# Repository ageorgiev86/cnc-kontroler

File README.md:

# CNC контролер на Orange Pi One

Универсален CNC контролер, изцяло собствена разработка: до 6 оси, шпиндел, магазин за инструменти, отделни входове за 3D пробник и toolsetter и затворен контур с енкодери.

Готовите програми (LinuxCNC, grblHAL, Mach3, arisc и др.) се използват само като справка за това как са решени отделните задачи. Кодът, протоколите и интерфейсът се пишат от нулата.

## Съдържание

| Файл | Какво има |
|---|---|
| [`LICENSE`](LICENSE) | Собственически лиценз: всички права запазени |
| [`THIRD_PARTY_NOTICES.md`](THIRD_PARTY_NOTICES.md) | Чужди компоненти, техните лицензи и правилата кодът да остане затворен |
| [`CLAUDE.md`](CLAUDE.md) | Кратък контекст за нови сесии с Claude Code: правила, решения, стил на работа |
| [`docs/arhitektura.md`](docs/arhitektura.md) | Хардуер, разделение Linux / MCU, енкодери, таймери, SPI протокол, периферия |
| [`docs/platki.md`](docs/platki.md) | Подходящи модели Orange Pi и Raspberry Pi, препоръки и правила за преносимост |
| [`docs/ui-iziskvania.md`](docs/ui-iziskvania.md) | Всички изисквания към интерфейса, екран по екран |
| [`docs/makrosi-logika.md`](docs/makrosi-logika.md) | Макроси, фонова логика и скриптове: разширение след стабилната версия |
| [`docs/otvoreni-vaprosi.md`](docs/otvoreni-vaprosi.md) | Неуточнени въпроси и следващи стъпки |
| [`docs/interpretator-planer.md`](docs/interpretator-planer.md) | Интерпретатор и планер на G-code: устройство, диалекти Mach3/Haas, стъпки |
| [`core/`](core/) | Ядро на C: интерпретатор и планер (тестове с `ctest`); инструкция в [`core/README.md`](core/README.md) |
| [`firmware/stm32/`](firmware/stm32/) | Firmware за STM32H723ZG (CMake, VS Code); инструкция в [`firmware/stm32/README.md`](firmware/stm32/README.md) |
| [`ui/maket.html`](ui/maket.html) | Интерактивен макет на интерфейса (отваря се в браузър) |

## Инсталиране на чиста система

На чист Armbian (Orange Pi) или Raspberry Pi OS Lite, като обикновения потребител:

```sh
sudo apt-get update && sudo apt-get install -y git
git clone https://github.com/ageorgiev86/cnc-kontroler.git
cd cnc-kontroler
sudo bash tools/cnc-install.sh            # интерфейсът, ядрото, услугата, USB, мрежата, логото
sudo reboot
```

Скриптът (`tools/cnc-install.sh`) пуска по ред отделните скриптове от `tools/`, компилира и проверява ядрото с тестовете му. Дневникът е в `install.log`. С `--readonly` включва и системата само за четене (за работа на машината), с `--no-splash` е без началния екран.

## Как се отваря макетът

Свали `ui/maket.html` и го отвори в браузър (Chrome, Edge, Firefox). Не е нужен сървър. Машината в макета е симулирана.

Публикувано копие (частно, вижда се само от собственика): https://claude.ai/artifact/83qwLJ9rhE3jGNBGYs3KNy

## Състояние

- [x] Избор на архитектура (Orange Pi / Raspberry Pi + STM32H723 по SPI)
- [x] Документация: архитектура, платки, входове и изходи 32 + 32, аналогови, RTC, лиценз
- [x] Интерактивен макет на интерфейса:
  - портретно и хоризонтално, 6 резолюции
  - фреза/рутер, лазер, плазма, струг; 3, 4 и 5 оси
  - позиции с енкодерна грешка, HOME, Go to 0, ръчно задаване на реф. точка
  - 3D траектория с цвят по инструмент
  - програми от памет, USB и мрежа; G-code с подпрограми (M98/M99), G81–83, G95/G96
  - Run from here с подготвителен ход, Rewind, изминало и оставащо време
  - магазин (карусел, верига, линеен), револвер за струг
  - пробинг (вкл. външен и вътрешен ъгъл), toolsetter
  - шпиндел по Modbus или PWM, входове и изходи 32 + 32, аналогови входове и изходи, мрежа
  - RESET (включване и реферирване), смазване, енкодери по оси, пробник встрани с калибриране
  - нива на достъп с PIN (Настройчик, Производител) и дневник на промените
- [ ] Armbian с PREEMPT_RT ядро и device tree overlays
- [ ] SPI протокол (спецификация)
- [x] Firmware за STM32: проект (CMake, HAL, такт, MPU, мигащ светодиод)
- [ ] Firmware за STM32: генериране на стъпки, енкодери, latch за пробник
- [ ] G-code интерпретатор и планер
- [ ] Истински интерфейс на LVGL
- [ ] Стабилна версия, тествана на машина
- [ ] Макроси и логика (обновяване)

Подробен план и отворени въпроси: [`docs/otvoreni-vaprosi.md`](docs/otvoreni-vaprosi.md).

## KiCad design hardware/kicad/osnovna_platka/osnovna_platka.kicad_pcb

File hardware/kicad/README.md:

# Платките (KiCad 10)

Схемите и разположението се **генерират със скриптове** (Python-а на KiCad), а не се чертаят на ръка. Така всяка промяна е повторяема и се проверява автоматично (ERC, DRC, застъпвания).

| Папка / файл | Какво е |
|---|---|
| `osnovna_platka/` | основната платка: STM32H723ZGT6, драйвери, енкодери, входове и изходи 8 + 8, шпиндел, Orange Pi (338 × 136 мм) |
| `razshiritel/` | разширителен модул: 8 входа + 8 изхода 24 V, верижно (93 × 64 мм) |
| `osnovna_platka.py` | схемата на основната платка (речникът `MCU` = изводите на STM32, съвпада с `firmware/stm32/Core/Inc/board.h`) |
| `platka.py` | разположението на основната платка по план (роли на елементите от схемата) |
| `razshiritel.py` | схемата и разположението на модула |
| `pravila.py` | правилата: класове мрежи (сигнал 0,4 мм, STM32 0,3 мм, захранване 1 мм, маси), преходи 0,6/1,2 мм |
| `trasirane.py` | пробно трасиране с Freerouting върху копие на проекта + заливки GND и GND_IO на двата слоя |
| `sch.py` | общата част на генератора на схеми |

## Пускане

Затвори KiCad без запис преди това (скриптовете презаписват файловете).

```
"C:\Program Files\KiCad\10.0\bin\python.exe" -I osnovna_platka.py osnovna_platka
"C:\Program Files\KiCad\10.0\bin\python.exe" -I pravila.py osnovna_platka
"C:\Program Files\KiCad\10.0\bin\python.exe" -I platka.py osnovna_platka 136
"C:\Program Files\KiCad\10.0\bin\python.exe" -I razshiritel.py razshiritel 64
```

Ако вече си трасирал или местил нещо ръчно в KiCad, **не пускай `platka.py`** (ще го изтрие). Промените по схемата тогава се пренасят с F8 (Update PCB from Schematic): връзката схема ↔ платка е по постоянни UUID.

## На Linux (и трасиране)

KiCad 10 от PPA-то на KiCad (Ubuntu 24.04), Java 21 и Freerouting 2.1.0 (2.5 иска Java 25):

```
sudo add-apt-repository ppa:kicad/kicad-10.0-releases
sudo apt install --no-install-recommends kicad kicad-footprints kicad-symbols openjdk-21-jre-headless
sudo mkdir -p /opt/freerouting
sudo curl -L -o /opt/freerouting/freerouting-2.1.0.jar \
    https://github.com/freerouting/freerouting/releases/download/v2.1.0/freerouting-2.1.0.jar
```

Скриптовете се пускат с Python-а, с който е компилиран модулът `pcbnew` (на Ubuntu 24.04 — `python3.12`):

```
python3.12 -I osnovna_platka.py osnovna_platka
python3.12 -I pravila.py osnovna_platka
python3.12 -I platka.py osnovna_platka 136
python3.12 -I trasirane.py osnovna_platka /tmp/trasirane --minutes 90
kicad-cli pcb drc --severity-all /tmp/trasirane/osnovna_platka.kicad_pcb
```

`trasirane.py` търси Freerouting и Java така: аргументите `--jar`/`--java`, после променливите
`FREEROUTING_JAR`/`FREEROUTING_JAVA`, после (Linux) най-новия `/opt/freerouting/freerouting-*.jar` и `java` от PATH,
(Windows) плъгина на KiCad. Пътищата до KiCad (символи, отпечатъци, `kicad-cli`) се сменят с `KICAD_DIR`,
`KICAD_SYMBOL_DIR`, `KICAD_FOOTPRINT_DIR`, `KICAD_CLI`. Ако ERC/DRC се оплакват „library not included“, копирай
`/usr/share/kicad/template/{sym,fp}-lib-table` в `~/.config/kicad/10.0/`.

Freerouting 2.1 не спира по броя проходи (`-mp` се пренебрегва), а само по време: `--minutes N` (или
`FREEROUTING_MINUTES`, по подразбиране 60). Напредъкът е в `<копие>/freerouting.log` („pass #… (N unrouted)“).
Преди Freerouting `trasirane.py` слага преходите към масата (при QFP навътре под корпуса) и заключени изводи навън
по 1,5 мм от всеки сигнален извод на STM32 (fan-out: иначе рано сложено трасе покрай изводите запушва изхода на
останалите); след него маха висящите парчета и пълни масите (клемите — плътно към заливката).

След Freerouting остатъкът се довършва с `doveshvane.py` (собствен рутер: мрежа 0,05 мм, A* на двата слоя,
разкъсване на чужди трасета до 3 мм от краищата; `doveshvane.c` се компилира при пускане с `cc`/`gcc`):

```
python3.12 -I doveshvane.py /tmp/trasirane/osnovna_platka.kicad_pcb /tmp/trasirane/dovarshena.kicad_pcb
```

Пази платката с най-малко несвързани и без грешки в DRC. Резултатът е в `osnovna_platka/trasirana/`.

`pravila.py` записва и `osnovna_platka.kicad_dru`: 0,2 мм при всичко в U1 (изводите на STM32 са на 0,2 мм един от друг
и при масата и неизползваните изводи).

## Правила за домашно производство

- Двуслойна, фоторезист; метализирани отвори; най-малкото свредло 0,5 мм → преход с отвор 0,6 мм и площадка 1,2 мм.
- 0,2 мм разстояние само при изводите на STM32 (LQFP144, стъпка 0,5 мм), иначе 0,25 мм.
- Масите (GND за логиката, GND_IO за изолираната 24 V част) са заливка на двата слоя и служат и като екран; между тях 2 мм по изолационната граница (пунктир на копринения слой).

## План на основната платка

- **Горе:** всички изходи: 6 драйвера (клеми +5V, STEP, DIR, ENA, ALM, GND), честотен регулатор, RS485, изходи 1–8.
- **Долу:** всички входове: 7 енкодера (+5V, 0V, A, B), MPG пулт (гнездо 2 × 3), авариен стоп на пулта, пробник/toolsetter/авариен стоп, крайни изключватели и HOME (14 клеми).
- **Вляво:** 24 V, PE, USB-B и захранването (в посоката на тока). **Вдясно:** 24 V за датчиците, входове 1–8, гнездо за разширителните модули.
- Клемите са едноетажни щепселни 5,08 мм (Phoenix MSTBA), 1 мм една от друга.
- Изходите и входовете са свързани по физическия ред на изводите на чиповете (без кръстосване): буферите към драйверите са 74ACT541 (проходни изводи); при 74HCT165 таблицата „клема → бит“ е в `board.h`.

## Преди производство

Схемата е проектирана по документацията на чиповете, но преди поръчка/изработка трябва да я прегледа човек с опит в платки. Отворено: окончателното трасиране и модулът на MPG пулта (последен).

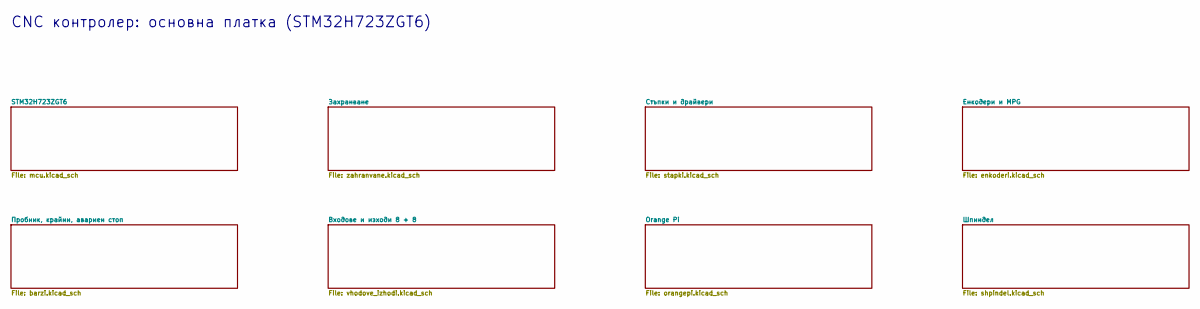
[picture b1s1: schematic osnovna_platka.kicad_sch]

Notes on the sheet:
CNC контролер: основна платка (STM32H723ZGT6)

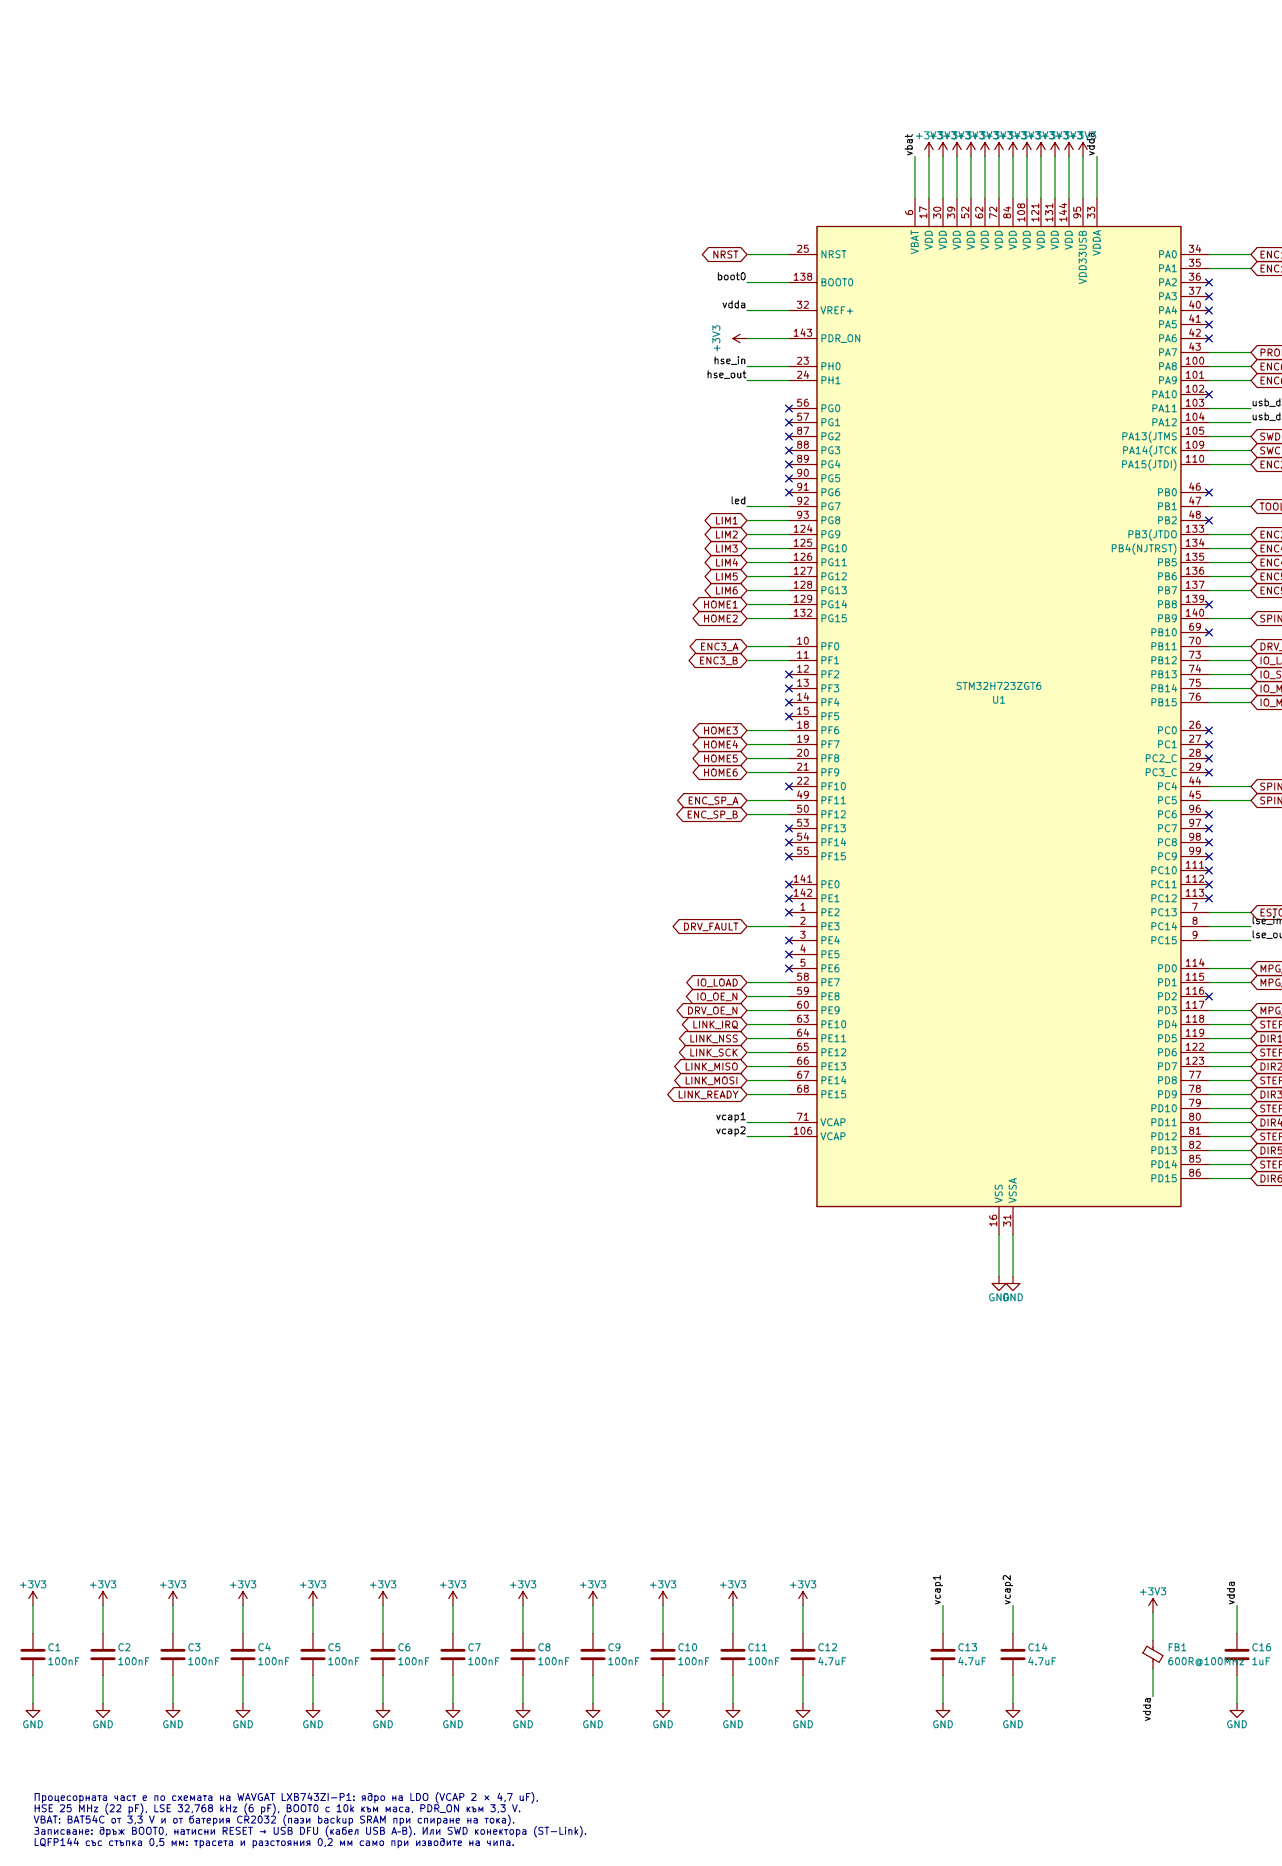
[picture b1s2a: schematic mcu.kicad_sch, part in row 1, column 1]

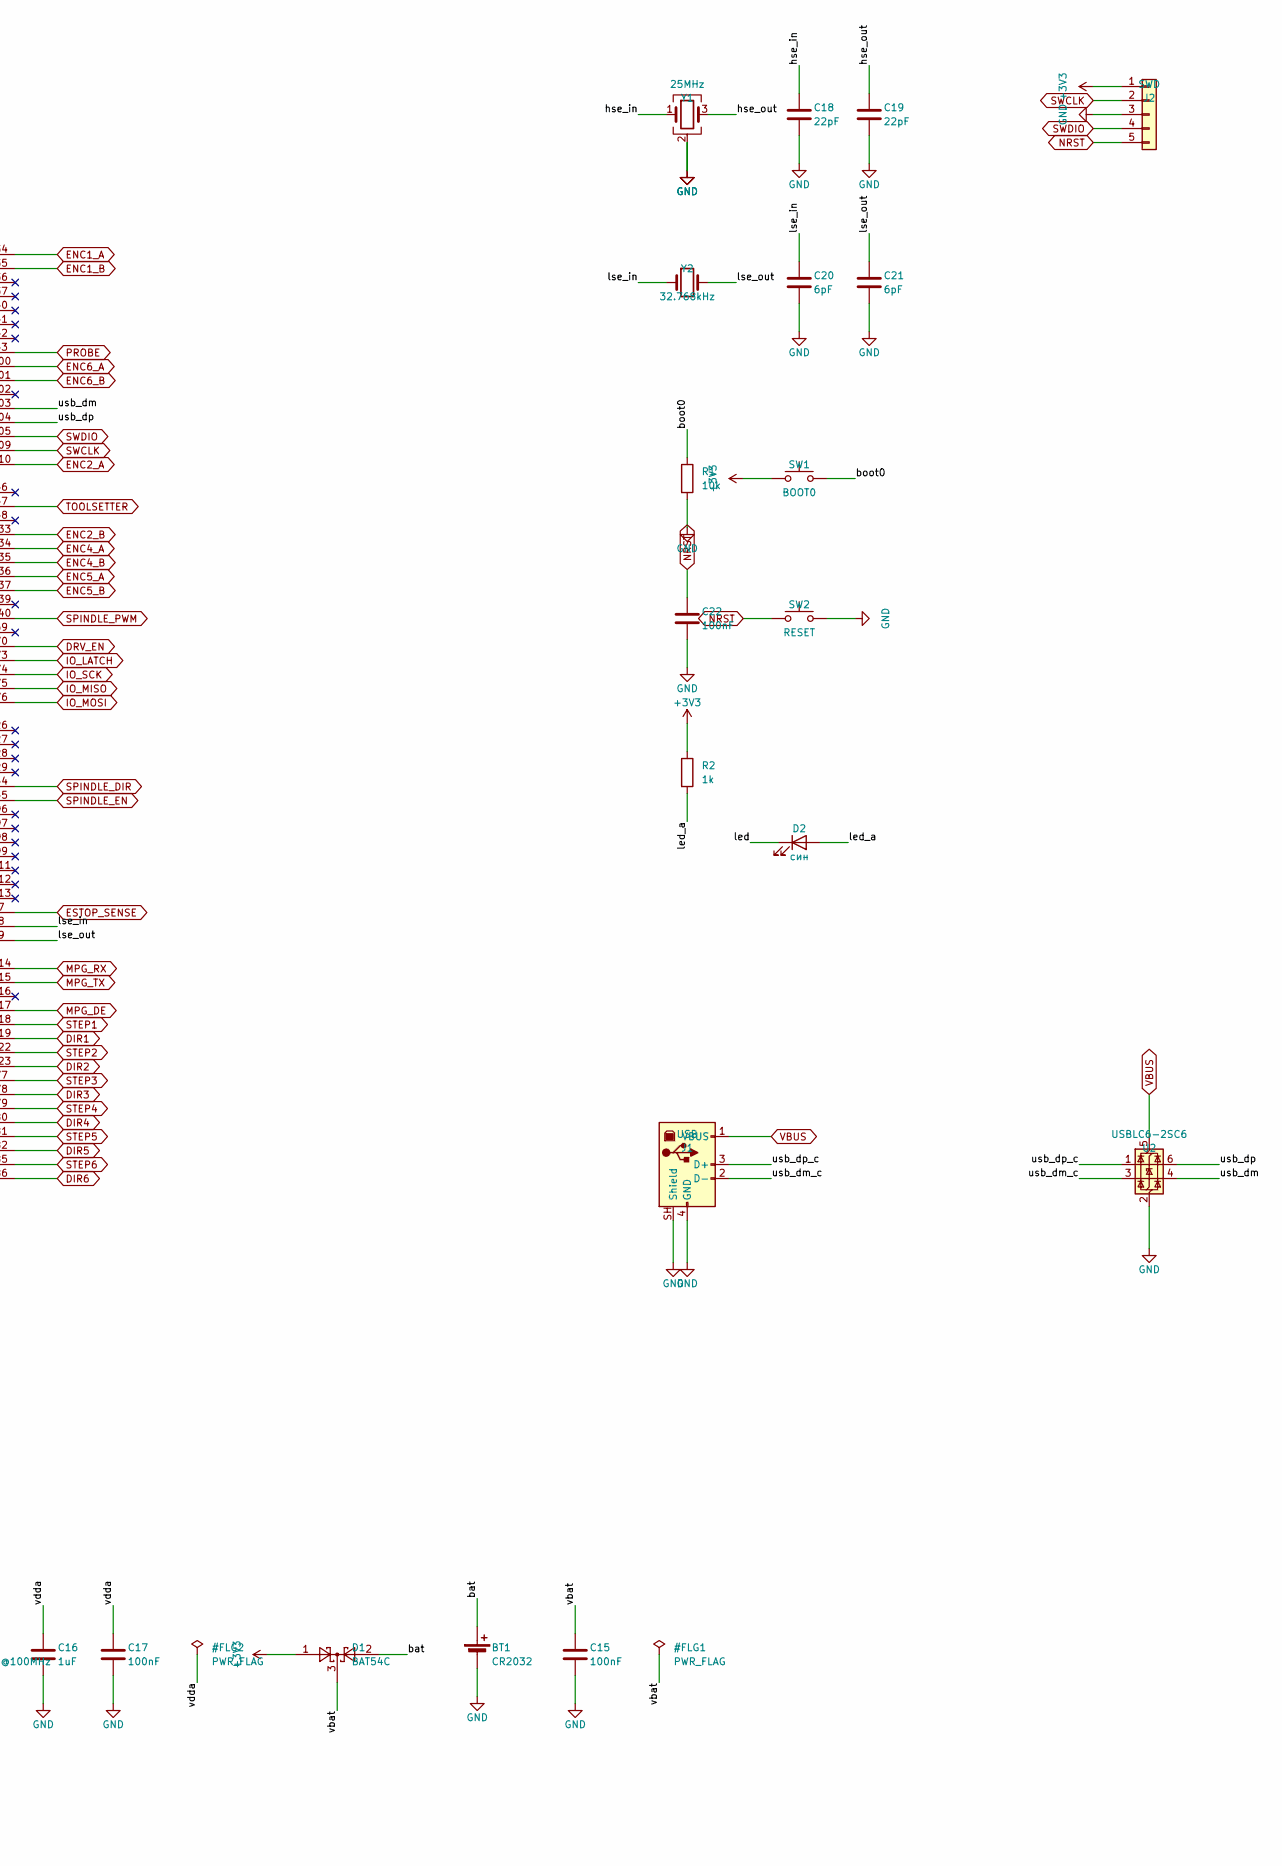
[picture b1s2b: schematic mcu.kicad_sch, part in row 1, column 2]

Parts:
BT1: CR2032; BatteryHolder_Keystone_3002_1x2032
C1, C2, C3, C4, C5, C6, C7, C8, C9, C10, C11, C15, C17, C22: 100nF; C_0805_2012Metric
C12, C13, C14: 4.7uF; C_1206_3216Metric
C16: 1uF; C_0805_2012Metric
C18, C19: 22pF; C_0805_2012Metric
C20, C21: 6pF; C_0805_2012Metric
D1: BAT54C; SOT-23
D2: син; LED_0805_2012Metric
FB1: 600R@100MHz; L_0805_2012Metric
J1: USB; USB_B_OST_USB-B1HSxx_Horizontal
J2: SWD; PinHeader_1x05_P2.54mm_Vertical
R1: 10k; R_0805_2012Metric
R2: 1k; R_0805_2012Metric
SW1: BOOT0; SW_SPST_TL3342
SW2: RESET; SW_SPST_TL3342
U1: STM32H723ZGT6; LQFP-144_20x20mm_P0.5mm
U2: USBLC6-2SC6; SOT-23-6
Y1: 25MHz; Crystal_SMD_3225-4Pin_3.2x2.5mm
Y2: 32.768kHz; Crystal_SMD_3215-2Pin_3.2x1.5mm

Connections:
+3V3: C1.1, C2.1, C3.1, C4.1, C5.1, C6.1, C7.1, C8.1, C9.1, C10.1, C11.1, C12.1, D1.1, FB1.1, J2.1, R2.1, SW1.1, U1.17 (VDD), U1.30 (VDD), U1.39 (VDD), U1.52 (VDD), U1.62 (VDD), U1.72 (VDD), U1.84 (VDD), U1.95 (VDD33USB), U1.108 (VDD), U1.121 (VDD), U1.131 (VDD), U1.143 (PDR_ON), U1.144 (VDD); also elsewhere on the board
/STM32H723ZGT6/bat: BT1.1 (+), D1.2
/STM32H723ZGT6/boot0: R1.1, SW1.2, U1.138 (BOOT0)
/STM32H723ZGT6/hse_in: C18.1, U1.23 (PH0), Y1.1
/STM32H723ZGT6/hse_out: C19.1, U1.24 (PH1), Y1.3
/STM32H723ZGT6/led: D2.1 (K), U1.92 (PG7)
/STM32H723ZGT6/led_a: D2.2 (A), R2.2
/STM32H723ZGT6/lse_in: C20.1, U1.8 (PC14), Y2.1
/STM32H723ZGT6/lse_out: C21.1, U1.9 (PC15), Y2.2
/STM32H723ZGT6/usb_dm: U1.103 (PA11), U2.4 (I/O2)
/STM32H723ZGT6/usb_dm_c: J1.2 (D-), U2.3 (I/O2)
/STM32H723ZGT6/usb_dp: U1.104 (PA12), U2.6 (I/O1)
/STM32H723ZGT6/usb_dp_c: J1.3 (D+), U2.1 (I/O1)
/STM32H723ZGT6/vbat: C15.1, D1.3, U1.6 (VBAT)
/STM32H723ZGT6/vcap1: C13.1, U1.71 (VCAP)
/STM32H723ZGT6/vcap2: C14.1, U1.106 (VCAP)
/STM32H723ZGT6/vdda: C16.1, C17.1, FB1.2, U1.32 (VREF+), U1.33 (VDDA)
DIR1: U1.119 (PD5); also elsewhere on the board
DIR2: U1.123 (PD7); also elsewhere on the board
DIR3: U1.78 (PD9); also elsewhere on the board
DIR4: U1.80 (PD11); also elsewhere on the board
DIR5: U1.82 (PD13); also elsewhere on the board
DIR6: U1.86 (PD15); also elsewhere on the board
DRV_EN: U1.70 (PB11); also elsewhere on the board
DRV_FAULT: U1.2 (PE3); also elsewhere on the board
DRV_OE_N: U1.60 (PE9); also elsewhere on the board
ENC1_A: U1.34 (PA0); also elsewhere on the board
ENC1_B: U1.35 (PA1); also elsewhere on the board
ENC2_A: U1.110 (PA15(JTDI)); also elsewhere on the board
ENC2_B: U1.133 (PB3(JTDO); also elsewhere on the board
ENC3_A: U1.10 (PF0); also elsewhere on the board
ENC3_B: U1.11 (PF1); also elsewhere on the board
ENC4_A: U1.134 (PB4(NJTRST)); also elsewhere on the board
ENC4_B: U1.135 (PB5); also elsewhere on the board
ENC5_A: U1.136 (PB6); also elsewhere on the board
ENC5_B: U1.137 (PB7); also elsewhere on the board
ENC6_A: U1.100 (PA8); also elsewhere on the board
ENC6_B: U1.101 (PA9); also elsewhere on the board
ENC_SP_A: U1.49 (PF11); also elsewhere on the board
ENC_SP_B: U1.50 (PF12); also elsewhere on the board
ESTOP_SENSE: U1.7 (PC13); also elsewhere on the board
GND: BT1.2 (-), C1.2, C2.2, C3.2, C4.2, C5.2, C6.2, C7.2, C8.2, C9.2, C10.2, C11.2, C12.2, C13.2, C14.2, C15.2, C16.2, C17.2, C18.2, C19.2, C20.2, C21.2, C22.2, J1.4 (GND), J1.SH (Shield), J2.3, R1.2, SW2.2, U1.16 (VSS), U1.31 (VSSA), U1.38 (VSS), U1.51 (VSS), U1.61 (VSS), U1.83 (VSS), U1.94 (VSS), U1.107 (VSS), U1.120 (VSS), U1.130 (VSS), U2.2 (GND), Y1.2 (G), Y1.4 (G); also elsewhere on the board
HOME1: U1.129 (PG14); also elsewhere on the board
HOME2: U1.132 (PG15); also elsewhere on the board
HOME3: U1.18 (PF6); also elsewhere on the board
HOME4: U1.19 (PF7); also elsewhere on the board
HOME5: U1.20 (PF8); also elsewhere on the board
HOME6: U1.21 (PF9); also elsewhere on the board
IO_LATCH: U1.73 (PB12); also elsewhere on the board
IO_LOAD: U1.58 (PE7); also elsewhere on the board
IO_MISO: U1.75 (PB14); also elsewhere on the board
IO_MOSI: U1.76 (PB15); also elsewhere on the board
IO_OE_N: U1.59 (PE8); also elsewhere on the board
IO_SCK: U1.74 (PB13); also elsewhere on the board
LIM1: U1.93 (PG8); also elsewhere on the board
LIM2: U1.124 (PG9); also elsewhere on the board
LIM3: U1.125 (PG10); also elsewhere on the board
LIM4: U1.126 (PG11); also elsewhere on the board
LIM5: U1.127 (PG12); also elsewhere on the board
LIM6: U1.128 (PG13); also elsewhere on the board
LINK_IRQ: U1.63 (PE10); also elsewhere on the board
LINK_MISO: U1.66 (PE13); also elsewhere on the board
LINK_MOSI: U1.67 (PE14); also elsewhere on the board
LINK_NSS: U1.64 (PE11); also elsewhere on the board
LINK_READY: U1.68 (PE15); also elsewhere on the board
LINK_SCK: U1.65 (PE12); also elsewhere on the board
MPG_DE: U1.117 (PD3); also elsewhere on the board
MPG_RX: U1.114 (PD0); also elsewhere on the board
MPG_TX: U1.115 (PD1); also elsewhere on the board
NRST: C22.1, J2.5, SW2.1, U1.25 (NRST)
PROBE: U1.43 (PA7); also elsewhere on the board
SPINDLE_DIR: U1.44 (PC4); also elsewhere on the board
SPINDLE_EN: U1.45 (PC5); also elsewhere on the board
SPINDLE_PWM: U1.140 (PB9); also elsewhere on the board
STEP1: U1.118 (PD4); also elsewhere on the board
STEP2: U1.122 (PD6); also elsewhere on the board
STEP3: U1.77 (PD8); also elsewhere on the board
STEP4: U1.79 (PD10); also elsewhere on the board
STEP5: U1.81 (PD12); also elsewhere on the board
STEP6: U1.85 (PD14); also elsewhere on the board
SWCLK: J2.2, U1.109 (PA14(JTCK)
SWDIO: J2.4, U1.105 (PA13(JTMS)
TOOLSETTER: U1.47 (PB1); also elsewhere on the board
VBUS: J1.1 (VBUS), U2.5 (VBUS); also elsewhere on the board

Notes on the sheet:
Процесорната част е по схемата на WAVGAT LXB743ZI-P1: ядро на LDO (VCAP 2 × 4,7 uF), HSE 25 MHz (22 pF), LSE 32,768 kHz (6 pF), BOOT0 с 10k към маса, PDR_ON към 3,3 V. VBAT: BAT54C от 3,3 V и от батерия CR2032 (пази backup SRAM при спиране на тока). Записване: дръж BOOT0, натисни RESET → USB DFU (к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

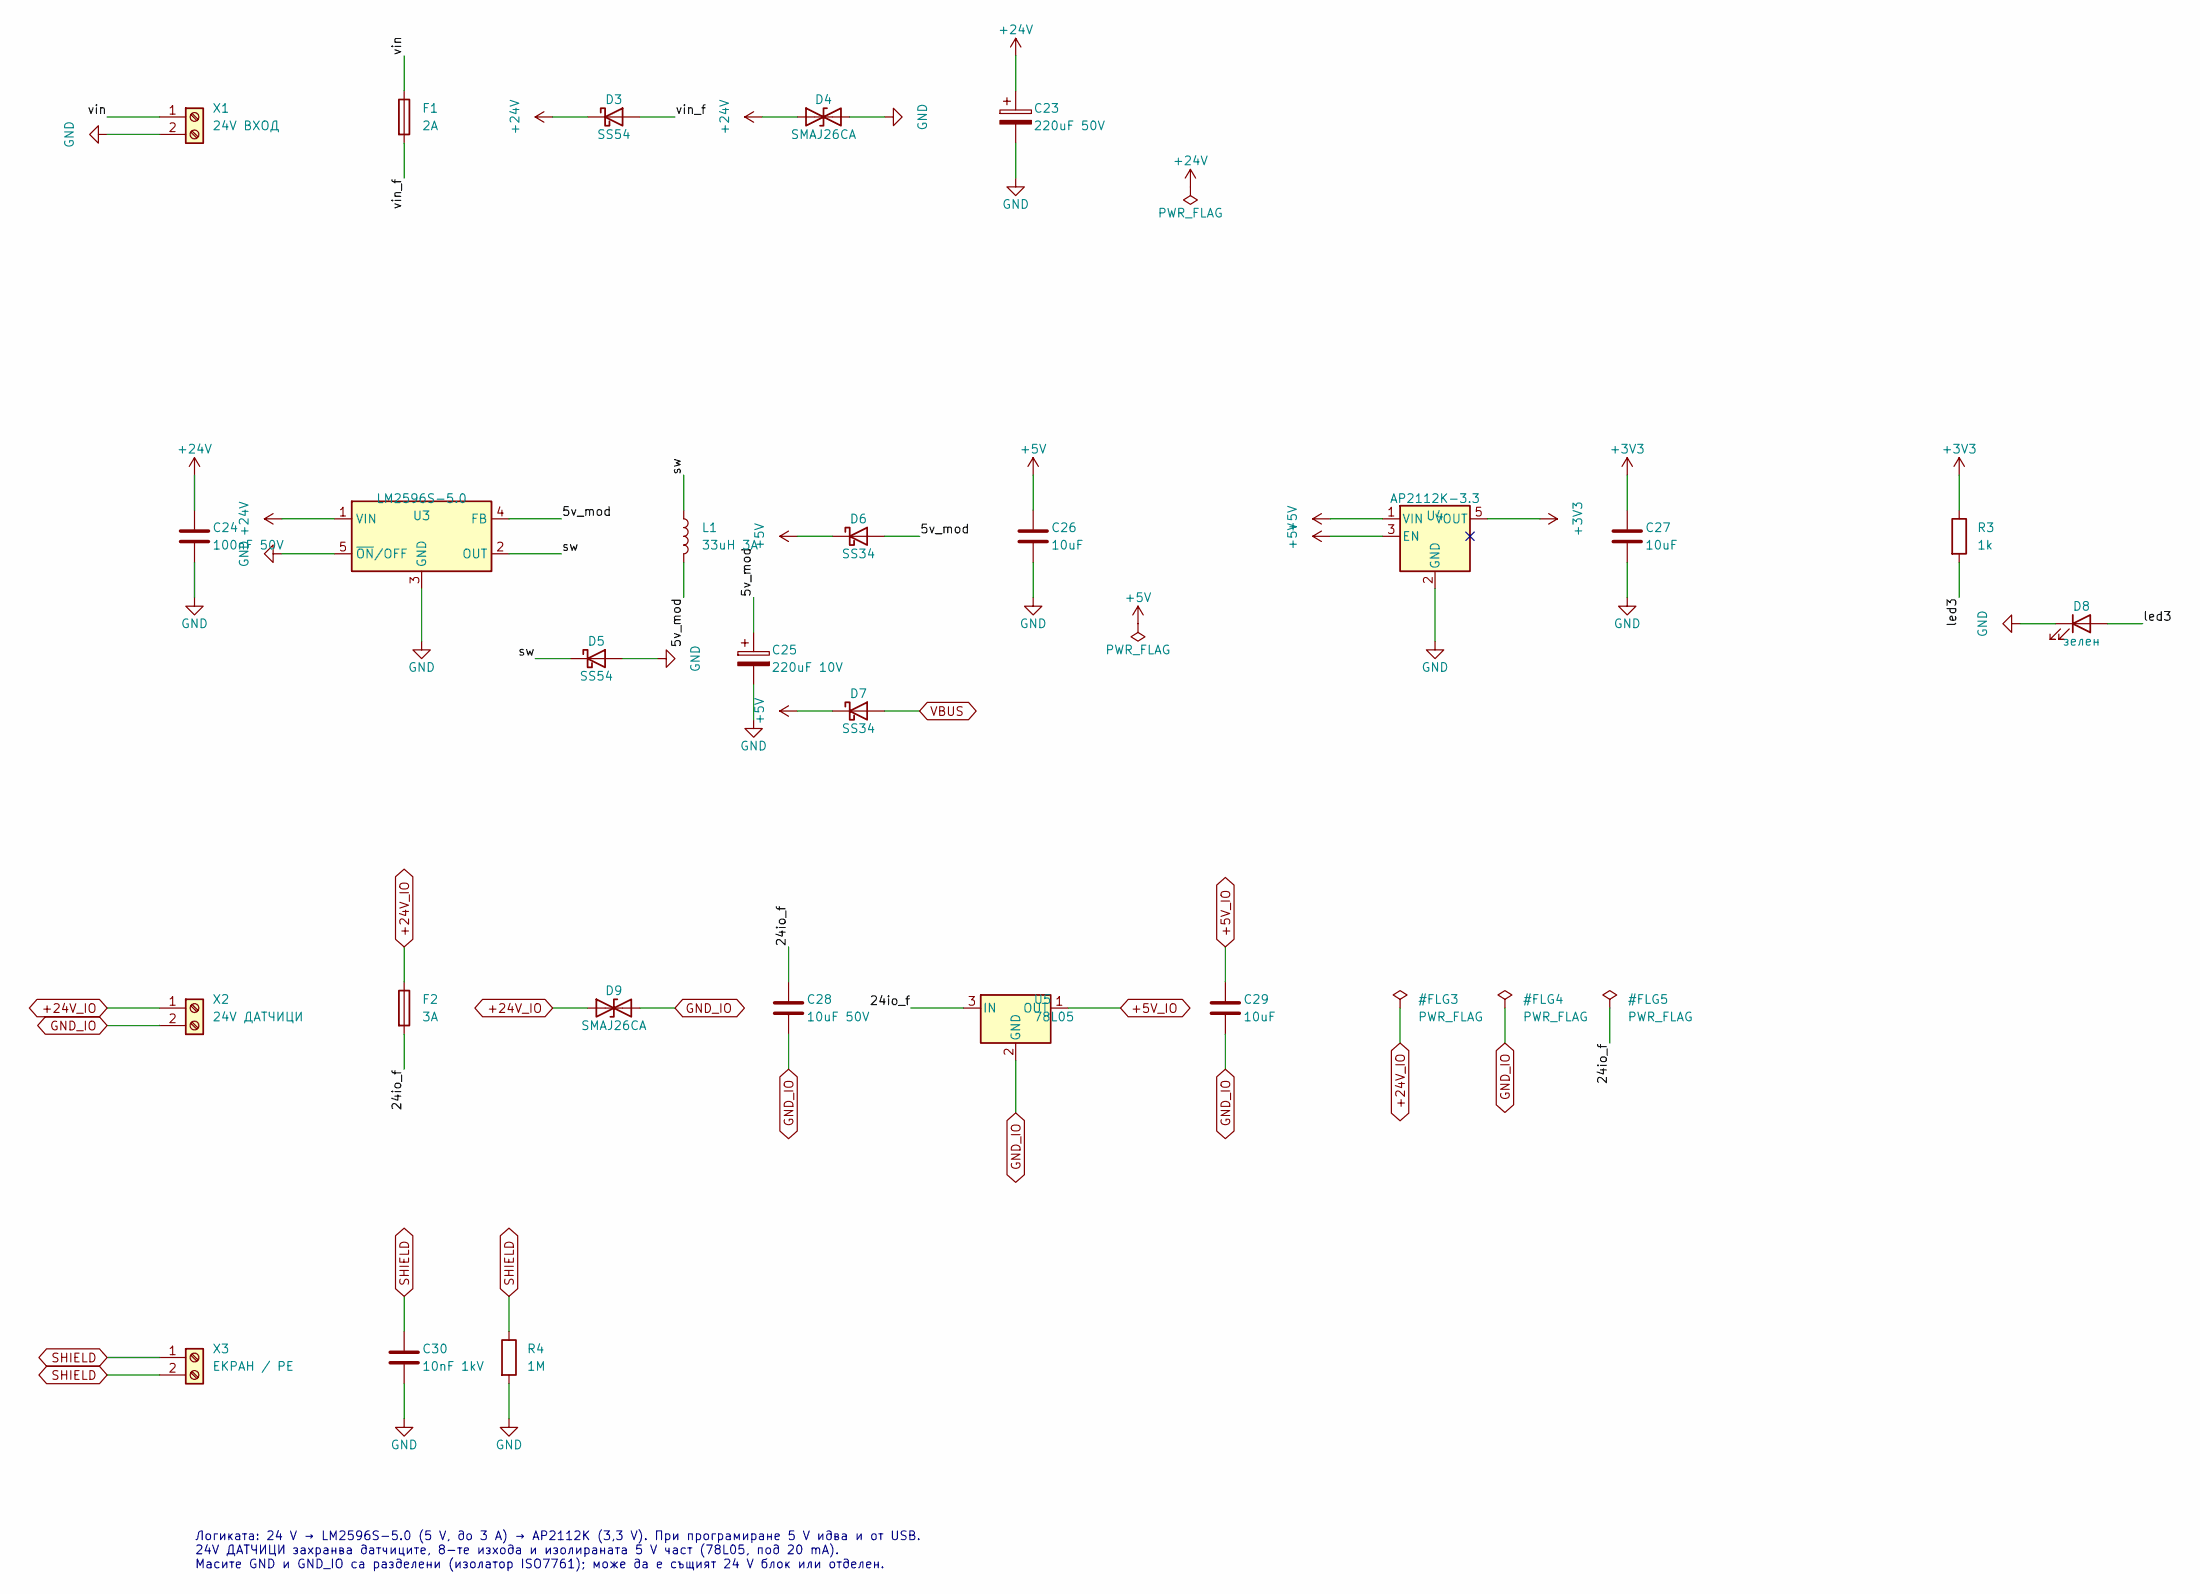
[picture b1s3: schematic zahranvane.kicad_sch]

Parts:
C23: 220uF 50V; CP_Elec_10x10.5
C24: 100nF 50V; C_0805_2012Metric
C25: 220uF 10V; CP_Elec_8x10
C26, C27, C29: 10uF; C_1206_3216Metric
C28: 10uF 50V; C_1210_3225Metric
C30: 10nF 1kV; C_1206_3216Metric
D3, D5: SS54; D_SMC
D4, D9: SMAJ26CA; D_SMA
D6, D7: SS34; D_SMA
D8: зелен; LED_0805_2012Metric
F1: 2A; Fuse_1812_4532Metric
F2: 3A; Fuse_1812_4532Metric
L1: 33uH 3A; L_12x12mm_H8mm
R3: 1k; R_0805_2012Metric
R4: 1M; R_1206_3216Metric
U3: LM2596S-5.0; TO-263-5_TabPin3
U4: AP2112K-3.3; SOT-23-5
U5: 78L05; SOT-89-3
X1: 24V ВХОД; PhoenixContact_MSTBA_2,5_2-G-5,08_1x02_P5.08mm_Horizontal
X2: 24V ДАТЧИЦИ; PhoenixContact_MSTBA_2,5_2-G-5,08_1x02_P5.08mm_Horizontal
X3: ЕКРАН / PE; PhoenixContact_MSTBA_2,5_2-G-5,08_1x02_P5.08mm_Horizontal

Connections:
+3V3: C27.1, R3.1, U4.5 (VOUT); also elsewhere on the board
+5V: C26.1, D6.1 (K), D7.1 (K), U4.1 (VIN), U4.3 (EN); also elsewhere on the board
+5V_IO: C29.1, U5.1 (OUT); also elsewhere on the board
+24V: C23.1, C24.1, D3.1 (K), D4.1 (A1), U3.1 (VIN); also elsewhere on the board
+24V_IO: D9.1 (A1), F2.1, X2.1; also elsewhere on the board
/Захранване/5v_mod: C25.1, D6.2 (A), L1.2, U3.4 (FB)
/Захранване/24io_f: C28.1, F2.2, U5.3 (IN)
/Захранване/led3: D8.2 (A), R3.2
/Захранване/sw: D5.1 (K), L1.1, U3.2 (OUT)
/Захранване/vin: F1.1, X1.1
/Захранване/vin_f: D3.2 (A), F1.2
GND: C23.2, C24.2, C25.2, C26.2, C27.2, C30.2, D4.2 (A2), D5.2 (A), D8.1 (K), R4.2, U3.3 (GND), U3.5 (~ON/OFF), U4.2 (GND), X1.2; also elsewhere on the board
GND_IO: C28.2, C29.2, D9.2 (A2), U5.2 (GND), X2.2; also elsewhere on the board
SHIELD: C30.1, R4.1, X3.1, X3.2
VBUS: D7.2 (A); also elsewhere on the board

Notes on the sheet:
Логиката: 24 V → LM2596S-5.0 (5 V, до 3 A) → AP2112K (3,3 V). При програмиране 5 V идва и от USB. 24V ДАТЧИЦИ захранва датчиците, 8-те изхода и изолираната 5 V част (78L05, под 20 mA). Масите GND и GND_IO са разделени (изолатор ISO7761); може да е същият 24 V блок или отделен.

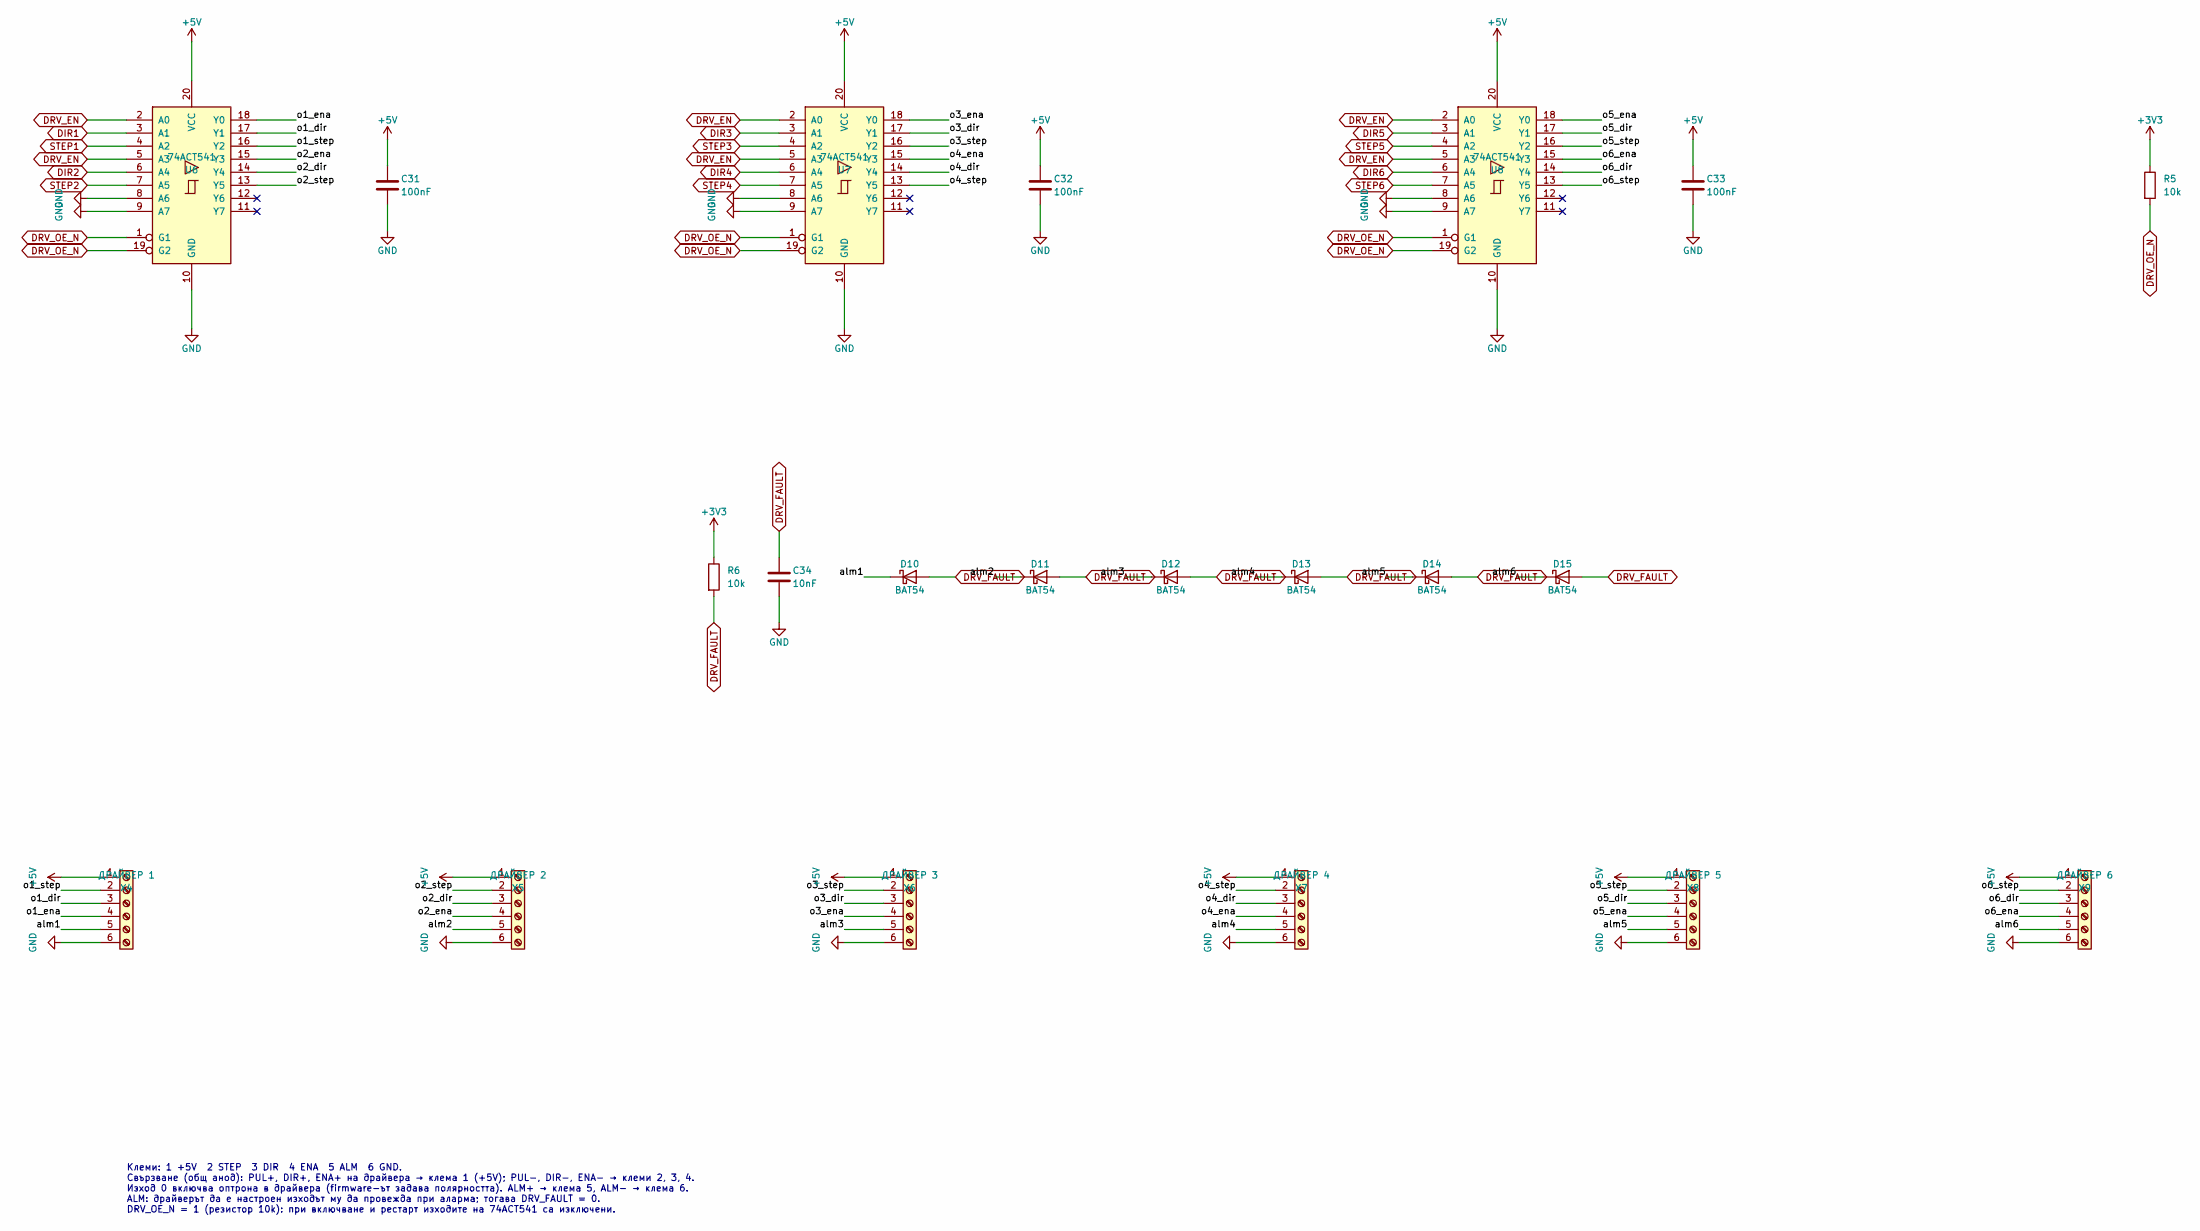
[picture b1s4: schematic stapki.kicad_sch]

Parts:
C31, C32, C33: 100nF; C_0805_2012Metric
C34: 10nF; C_0805_2012Metric
D10, D11, D12, D13, D14, D15: BAT54; D_SOD-323
R5, R6: 10k; R_0805_2012Metric
U6, U7, U8: 74ACT541; SOIC-20W_7.5x12.8mm_P1.27mm
X4: ДРАЙВЕР 1; PhoenixContact_MSTBA_2,5_6-G-5,08_1x06_P5.08mm_Horizontal
X5: ДРАЙВЕР 2; PhoenixContact_MSTBA_2,5_6-G-5,08_1x06_P5.08mm_Horizontal
X6: ДРАЙВЕР 3; PhoenixContact_MSTBA_2,5_6-G-5,08_1x06_P5.08mm_Horizontal
X7: ДРАЙВЕР 4; PhoenixContact_MSTBA_2,5_6-G-5,08_1x06_P5.08mm_Horizontal
X8: ДРАЙВЕР 5; PhoenixContact_MSTBA_2,5_6-G-5,08_1x06_P5.08mm_Horizontal
X9: ДРАЙВЕР 6; PhoenixContact_MSTBA_2,5_6-G-5,08_1x06_P5.08mm_Horizontal

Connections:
+3V3: R5.1, R6.1; also elsewhere on the board
+5V: C31.1, C32.1, C33.1, U6.20 (VCC), U7.20 (VCC), U8.20 (VCC), X4.1, X5.1, X6.1, X7.1, X8.1, X9.1; also elsewhere on the board
/Стъпки и драйвери/alm1: D10.1 (K), X4.5
/Стъпки и драйвери/alm2: D11.1 (K), X5.5
/Стъпки и драйвери/alm3: D12.1 (K), X6.5
/Стъпки и драйвери/alm4: D13.1 (K), X7.5
/Стъпки и драйвери/alm5: D14.1 (K), X8.5
/Стъпки и драйвери/alm6: D15.1 (K), X9.5
/Стъпки и драйвери/o1_dir: U6.17 (Y1), X4.3
/Стъпки и драйвери/o1_ena: U6.18 (Y0), X4.4
/Стъпки и драйвери/o1_step: U6.16 (Y2), X4.2
/Стъпки и драйвери/o2_dir: U6.14 (Y4), X5.3
/Стъпки и драйвери/o2_ena: U6.15 (Y3), X5.4
/Стъпки и драйвери/o2_step: U6.13 (Y5), X5.2
/Стъпки и драйвери/o3_dir: U7.17 (Y1), X6.3
/Стъпки и драйвери/o3_ena: U7.18 (Y0), X6.4
/Стъпки и драйвери/o3_step: U7.16 (Y2), X6.2
/Стъпки и драйвери/o4_dir: U7.14 (Y4), X7.3
/Стъпки и драйвери/o4_ena: U7.15 (Y3), X7.4
/Стъпки и драйвери/o4_step: U7.13 (Y5), X7.2
/Стъпки и драйвери/o5_dir: U8.17 (Y1), X8.3
/Стъпки и драйвери/o5_ena: U8.18 (Y0), X8.4
/Стъпки и драйвери/o5_step: U8.16 (Y2), X8.2
/Стъпки и драйвери/o6_dir: U8.14 (Y4), X9.3
/Стъпки и драйвери/o6_ena: U8.15 (Y3), X9.4
/Стъпки и драйвери/o6_step: U8.13 (Y5), X9.2
DIR1: U6.3 (A1); also elsewhere on the board
DIR2: U6.6 (A4); also elsewhere on the board
DIR3: U7.3 (A1); also elsewhere on the board
DIR4: U7.6 (A4); also elsewhere on the board
DIR5: U8.3 (A1); also elsewhere on the board
DIR6: U8.6 (A4); also elsewhere on the board
DRV_EN: U6.2 (A0), U6.5 (A3), U7.2 (A0), U7.5 (A3), U8.2 (A0), U8.5 (A3); also elsewhere on the board
DRV_FAULT: C34.1, D10.2 (A), D11.2 (A), D12.2 (A), D13.2 (A), D14.2 (A), D15.2 (A), R6.2; also elsewhere on the board
DRV_OE_N: R5.2, U6.1 (G1), U6.19 (G2), U7.1 (G1), U7.19 (G2), U8.1 (G1), U8.19 (G2); also elsewhere on the board
GND: C31.2, C32.2, C33.2, C34.2, U6.8 (A6), U6.9 (A7), U6.10 (GND), U7.8 (A6), U7.9 (A7), U7.10 (GND), U8.8 (A6), U8.9 (A7), U8.10 (GND), X4.6, X5.6, X6.6, X7.6, X8.6, X9.6; also elsewhere on the board
STEP1: U6.4 (A2); also elsewhere on the board
STEP2: U6.7 (A5); also elsewhere on the board
STEP3: U7.4 (A2); also elsewhere on the board
STEP4: U7.7 (A5); also elsewhere on the board
STEP5: U8.4 (A2); also elsewhere on the board
STEP6: U8.7 (A5); also elsewhere on the board

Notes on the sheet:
Клеми: 1 +5V 2 STEP 3 DIR 4 ENA 5 ALM 6 GND. Свързване (общ анод): PUL+, DIR+, ENA+ на драйвера → клема 1 (+5V); PUL−, DIR−, ENA− → клеми 2, 3, 4. Изход 0 включва оптрона в драйвера (firmware-ът задава полярността). ALM+ → клема 5, ALM− → клема 6. ALM: драйверът да е настроен изходът му да провежда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
